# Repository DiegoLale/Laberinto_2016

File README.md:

# Laberinto_2016
Simple robot para competición de laberinto de la OSHWDem

Toda la información en www.lalebots.com

***14 octubre 2016***

  Creación del repositorio
  
  Añadido primer chasis
  
***16 octubre 2016***

  Modificado chasis
  
    chasisSuperior_v2
    cahsisInferior_v2
    
  Añadidas nuevas piezas
  
    bolaLoca
    TapaBateria
    LlantaLego
    
*** 24 octubre 2016***

  Compartida electrónica

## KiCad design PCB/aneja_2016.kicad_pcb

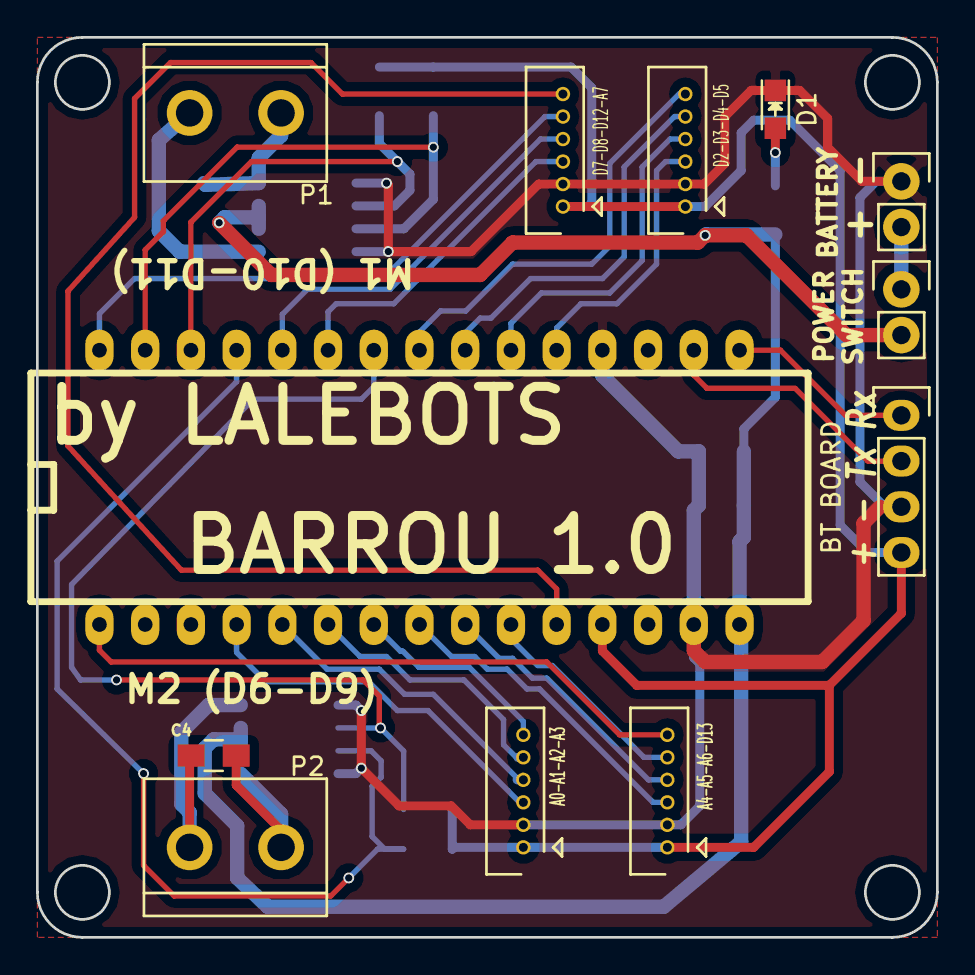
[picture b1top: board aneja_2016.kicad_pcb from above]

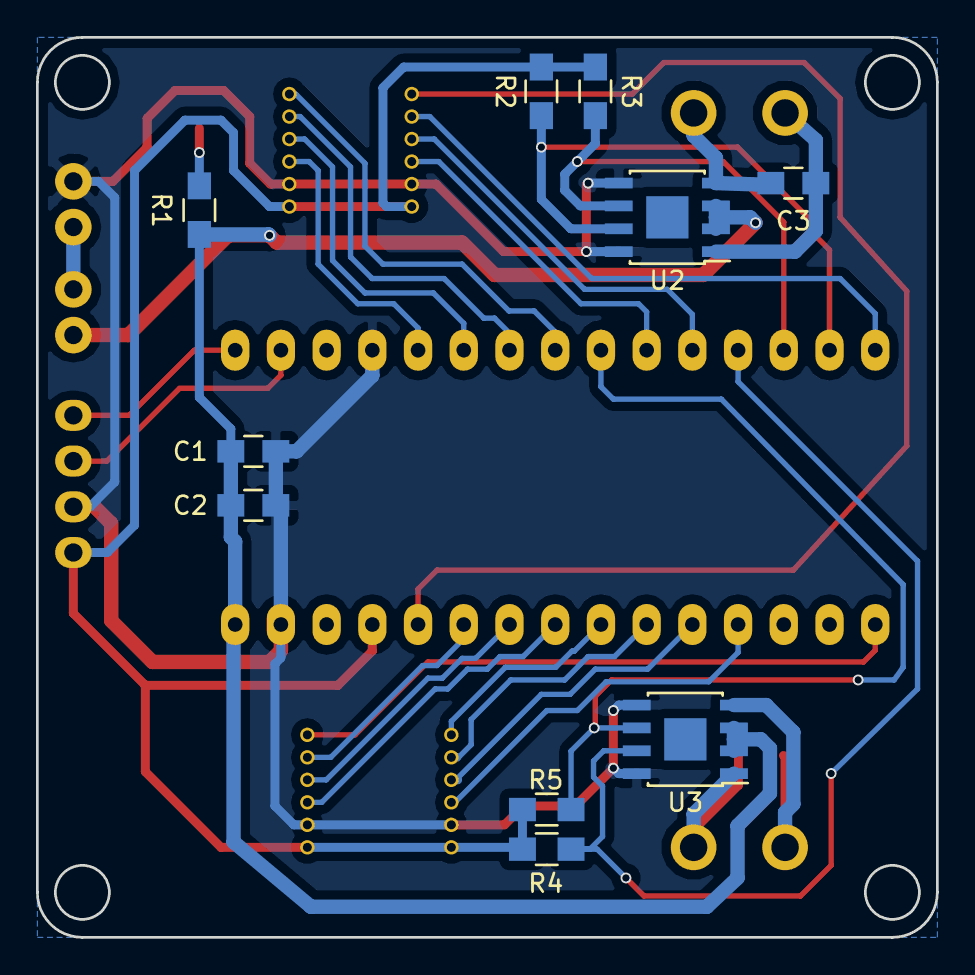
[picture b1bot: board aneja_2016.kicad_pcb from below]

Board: 2 copper layers, 50.0 x 50.0 mm, 22 parts (10 on the bottom side), 31 nets.

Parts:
A0-A1-A2-A3, A4-A5-A6-D13: CONN_01X06; Connector_Molex_PicoBlade_53047-0610
BT BOARD: BT_BOARD; Socket_Strip_Straight_1x04
C1, C2, C3, C4: C; C_0805_HandSoldering
D1: LED; LED-0805
D2-D3-D4-D5, D7-D8-D12-A7: CONN_01X06; Connector_Molex_PicoBlade_53047-0610
P1, P2: CONN_01X02; bornier2
P4, P5: CONN_01X02; Pin_Header_Straight_1x02
R1, R2, R3, R4, R5: R; R_0805_HandSoldering
U2, U3: hg7881; SOIC-8-1EP_3.9x4.9mm_Pitch1.27mm
by LALEBOTS: BARROU 1.0; arduino_mini

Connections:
/5v: A0-A1-A2-A3.1, A4-A5-A6-D13.1, BT BOARD.4, D2-D3-D4-D5.1, D7-D8-D12-A7.1, R2.1, R3.1, R4.1, R5.1, by LALEBOTS.12
/A0: A0-A1-A2-A3.3, by LALEBOTS.4
/A1: A0-A1-A2-A3.4, by LALEBOTS.5
/A2: A0-A1-A2-A3.5, by LALEBOTS.6
/A3: A0-A1-A2-A3.6, by LALEBOTS.7
/A4: A4-A5-A6-D13.3, by LALEBOTS.8
/A5: A4-A5-A6-D13.4, by LALEBOTS.9
/A6: A4-A5-A6-D13.5, by LALEBOTS.10
/A7: D7-D8-D12-A7.6, by LALEBOTS.11
/D2: D2-D3-D4-D5.3, by LALEBOTS.20
/D3: D2-D3-D4-D5.4, by LALEBOTS.21
/D4: D2-D3-D4-D5.5, by LALEBOTS.22
/D5: D2-D3-D4-D5.6, by LALEBOTS.23
/D7: D7-D8-D12-A7.3, by LALEBOTS.25
/D8: D7-D8-D12-A7.4, by LALEBOTS.26
/D12: D7-D8-D12-A7.5, by LALEBOTS.30
/D13: A4-A5-A6-D13.6, by LALEBOTS.1
/M1_a: R2.2, U2.7, by LALEBOTS.29
/M1_b: R3.2, U2.6, by LALEBOTS.28
/M2_a: R4.2, U3.7, by LALEBOTS.27
/M2_b: R5.2, U3.6, by LALEBOTS.24
/RX_arduino: BT BOARD.2, by LALEBOTS.17
/TX_arduino: BT BOARD.1, by LALEBOTS.16
/VIN: C1.1, C2.1, P5.2, R1.1, U2.2, U2.3, U3.2, U3.3, by LALEBOTS.15
GND: A0-A1-A2-A3.2, A4-A5-A6-D13.2, BT BOARD.3, C1.2, C2.2, D1.1, D2-D3-D4-D5.2, D7-D8-D12-A7.2, P4.1, U2.5, U2.8, U3.5, U3.8, by LALEBOTS.14, by LALEBOTS.19
unnamed: C3.1, P1.2, U2.1
unnamed: C3.2, P1.1, U2.4
unnamed: C4.1, P2.2, U3.1
unnamed: C4.2, P2.1, U3.4
unnamed: D1.2, R1.2
unnamed: P4.2, P5.1

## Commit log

2016-10-15 chasis inicial
2016-10-16 agregadas nuevas piezas
2016-10-16 piezas nuevas
2016-10-24 pcb compartida
2017-01-04 soportes
2017-10-20 piezas para laberinto
2017-10-20 piezas laberinto
2017-10-21 añadidas todas las piezas inprimibles o para corte laser del laberinto
